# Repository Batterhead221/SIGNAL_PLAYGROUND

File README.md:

# signal_playground
(LIGHT_BOARD_TOY)
KIDS TOY BUILT FOR MY NIECE / ANALOG PROJECT

For Emerson - Electronics Learning Board
A small interactive PCB I designed as a hands-on electronics toy for my niece.
An educational analog hardware project.

•	Resistor = brightness control
•	Capacitor = smoothing
•	Inductor = energy storage

Press the switches and watch how each component changes the LED response in real time.

Key Features
•	Interactive LED response to different passive components
•	Dedicated channels for resistors, capacitors, and inductors
•	Through-hole component interfaces for easy experimentation
•	Custom silkscreen artwork and educational labeling
•	2-layer PCB with ground plane for noise reduction

Hardware Design
•	CAD: KiCad
•	Power: 2xAA battery holder (3V)
•	Grounding: Top & Bottom copper pour with stitched ground vias
•	Input Path: Noise-optimized routing with short trace to input capacitor

This was my first project, so it's not the prettiest and there are alot of things that I would have done different now.
Oh well, it worked, and my niece loved it.

DESIGNED & ENGINEERED BY BRANDON SHELLY

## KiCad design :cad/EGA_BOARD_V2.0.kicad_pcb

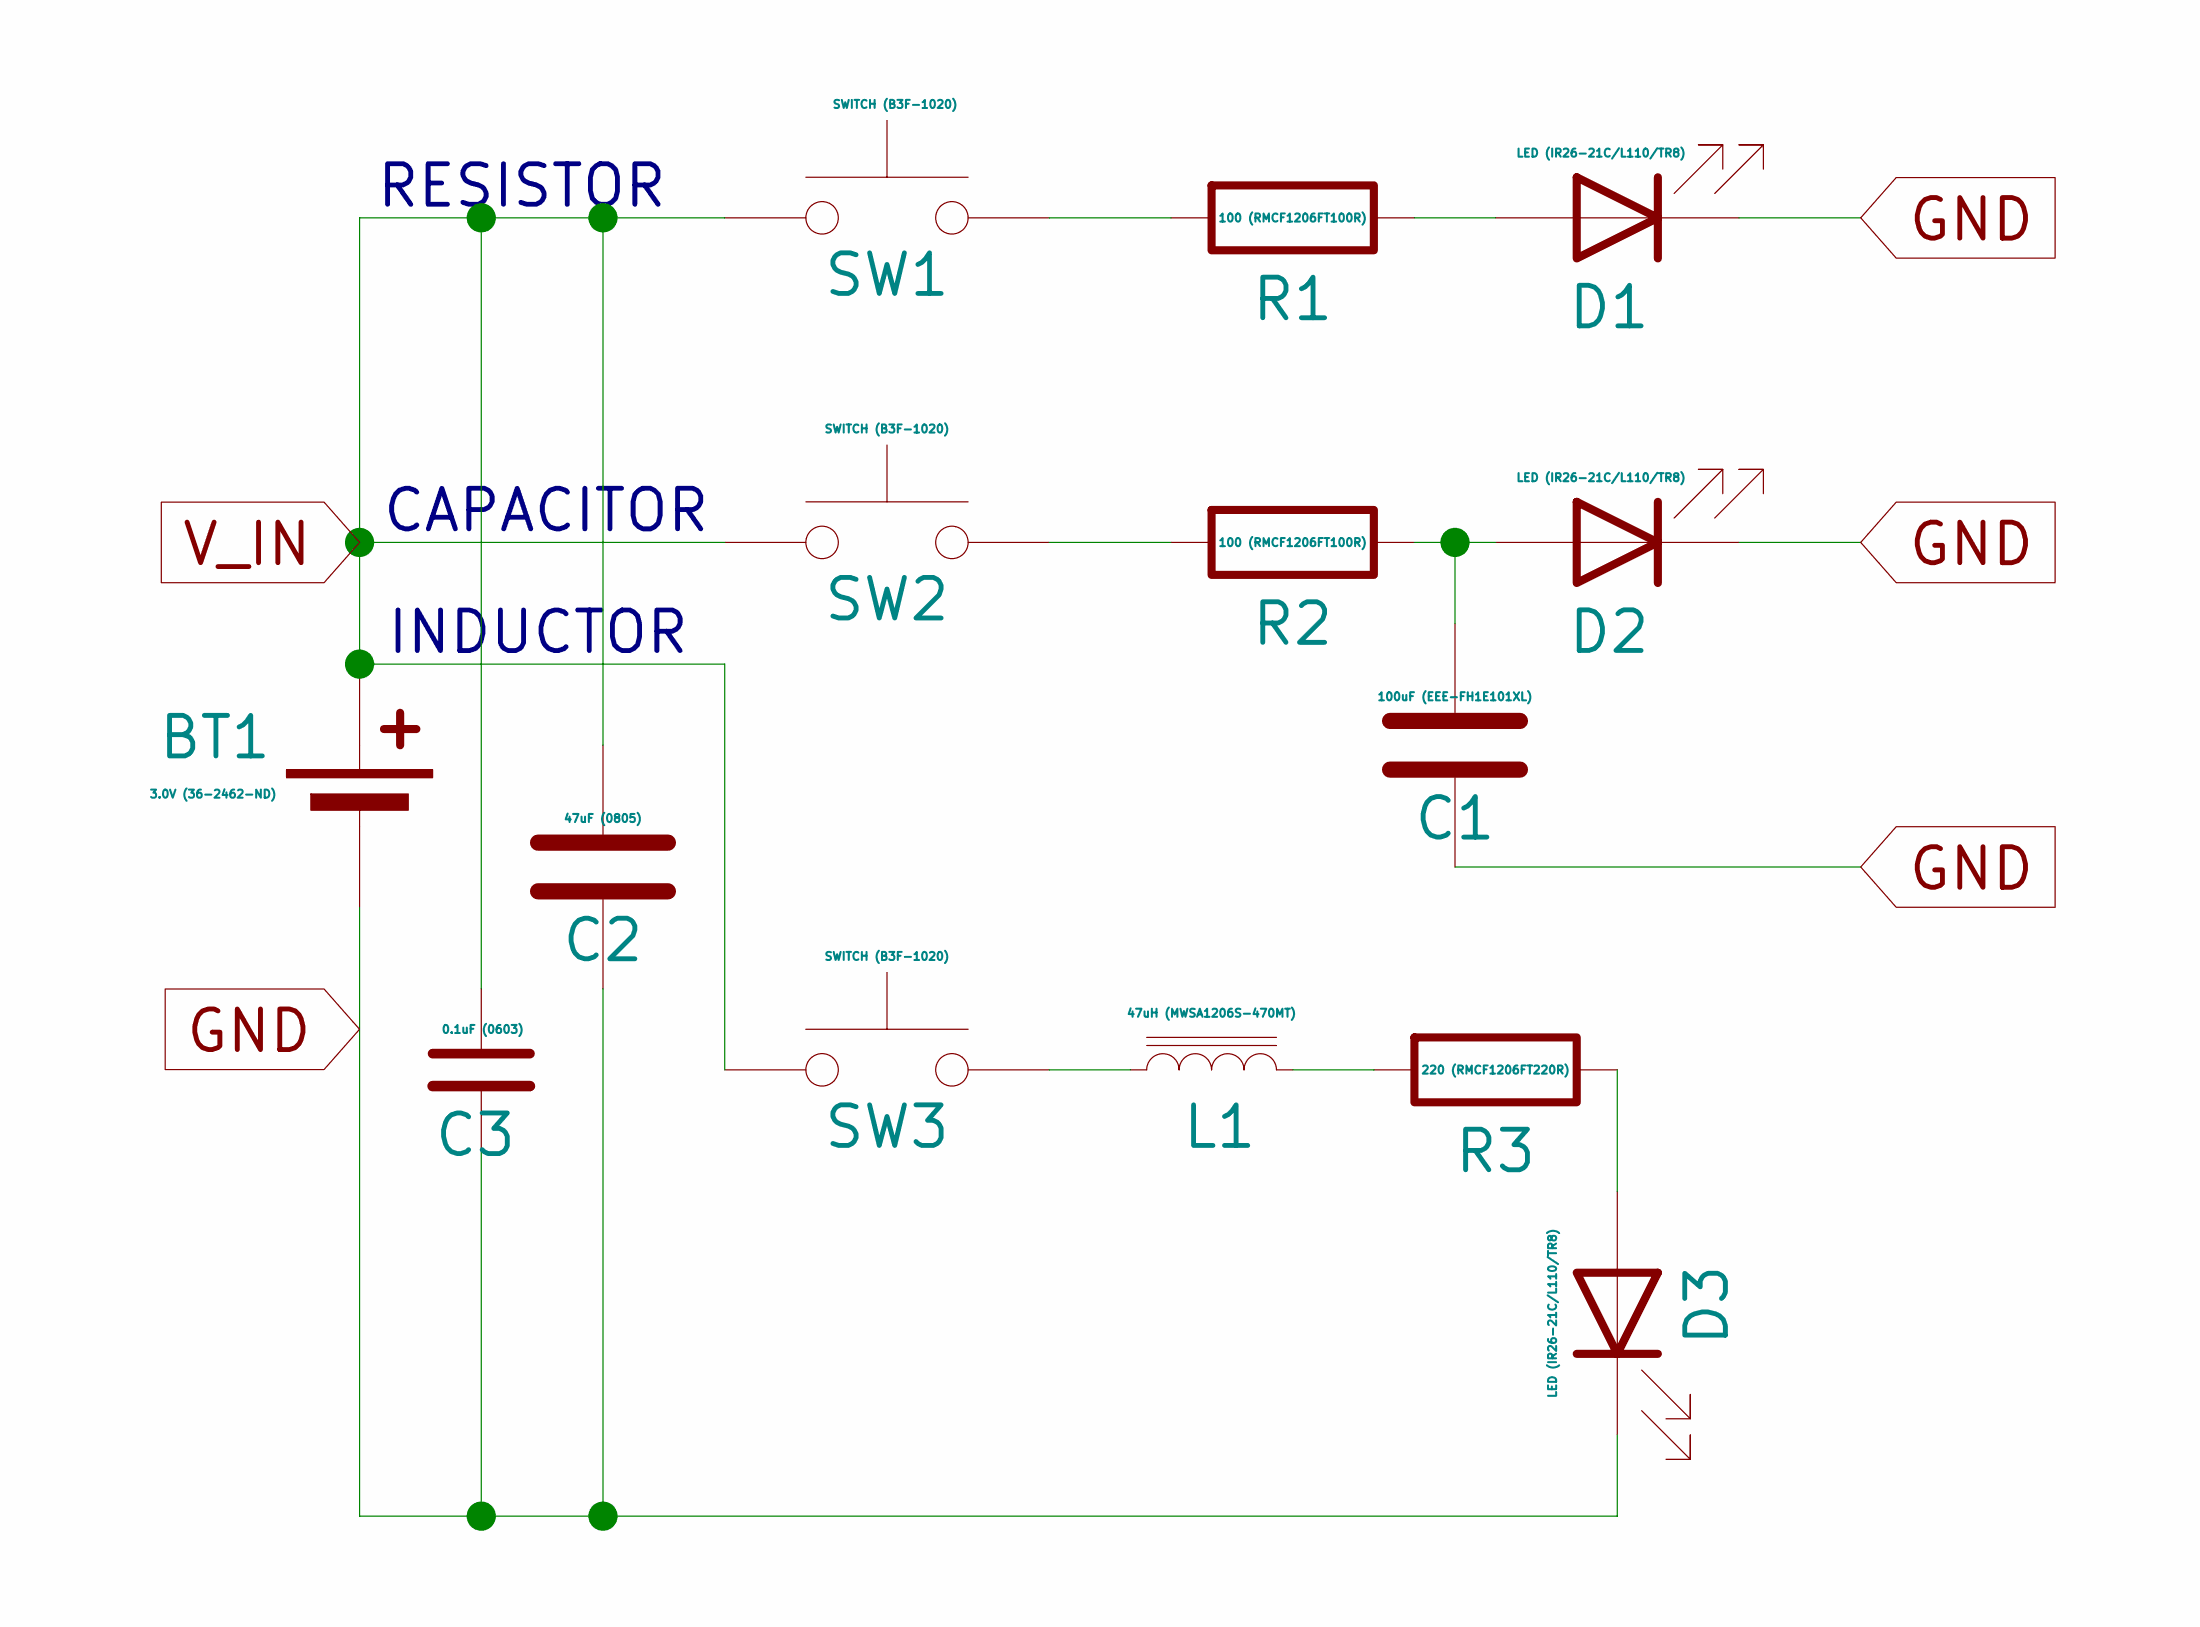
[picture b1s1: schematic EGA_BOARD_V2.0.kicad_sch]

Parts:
BT1: 3.0V (36-2462-ND); BatteryHolder_Keystone_2462_2xAA
C1: 100uF (EEE-FH1E101XL); C_Elec_5x5.8
C2: 47uF (0805); C_0805_2012Metric
C3: 0.1uF (0603); C_0603_1608Metric
D1, D2, D3: LED (IR26-21C/L110/TR8); LED_1206_3216Metric
L1: 47uH (MWSA1206S-470MT); L_Sunlord_MWSA1206S-3R3
R1, R2: 100 (RMCF1206FT100R); R_1206_3216Metric
R3: 220 (RMCF1206FT220R); R_1206_3216Metric
SW1, SW2, SW3: SWITCH (B3F-1020); SW_TH_Tactile_Omron_B3F-102x

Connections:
GND: BT1.2 (-), C1.2, C2.2, C3.2, D1.1 (K), D2.1 (K), D3.1 (K)
unnamed: D1.2 (A), R1.1
unnamed: C1.1, D2.2 (A), R2.1
unnamed: D3.2 (A), R3.1
unnamed: L1.1, SW3.2
unnamed: L1.2, R3.2
unnamed: R1.2, SW1.2
unnamed: R2.2, SW2.2
V_IN: BT1.1 (+), C2.1, C3.1, SW1.1, SW2.1, SW3.1

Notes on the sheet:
RESISTOR
INDUCTOR
CAPACITOR

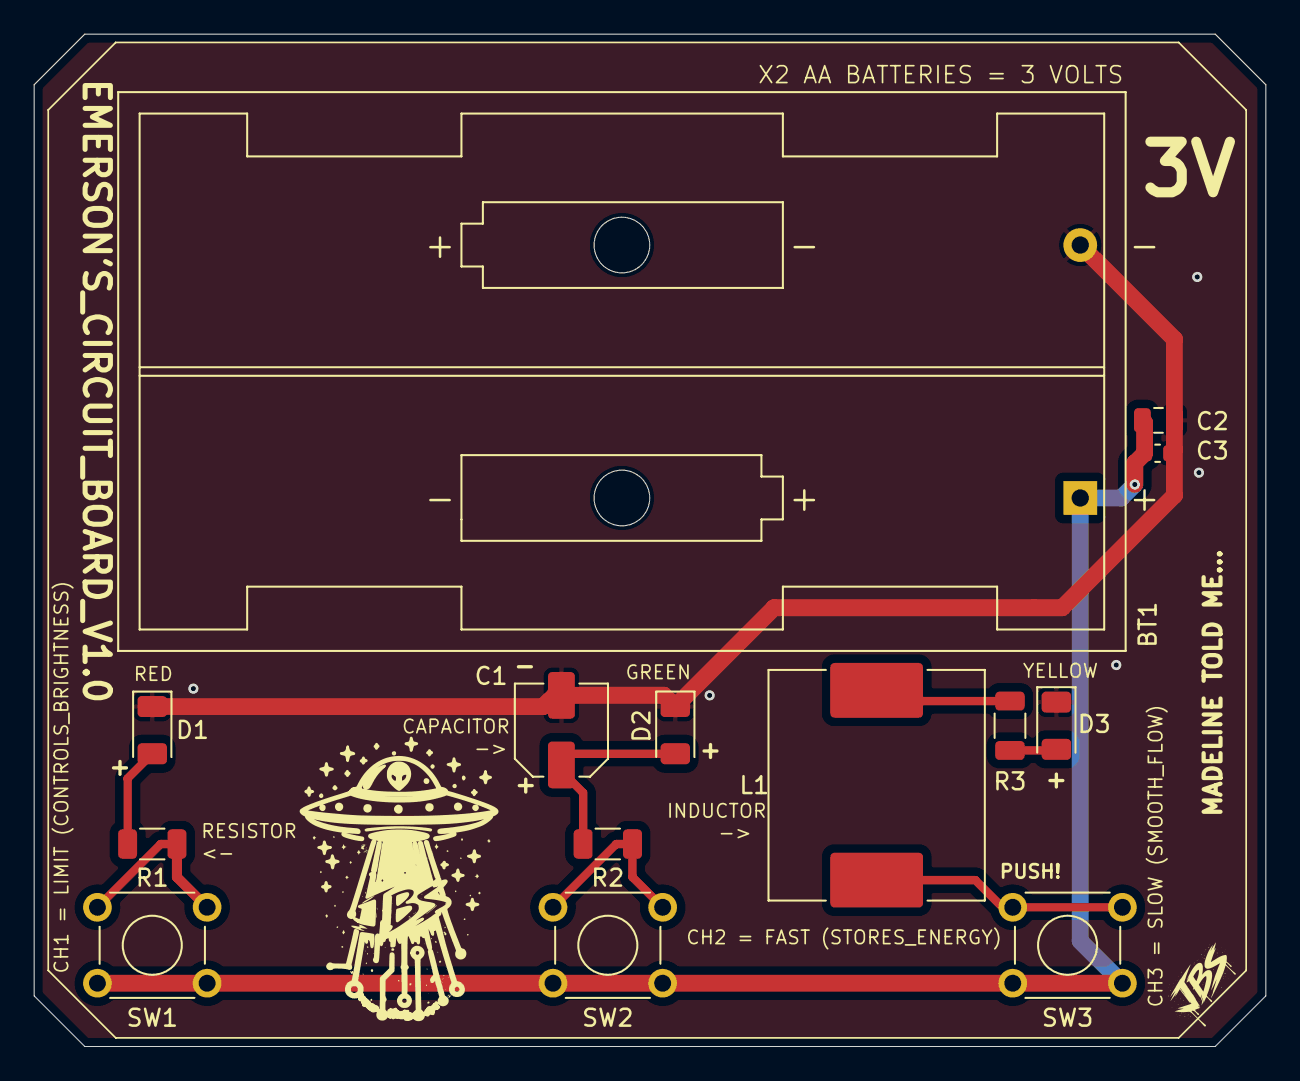
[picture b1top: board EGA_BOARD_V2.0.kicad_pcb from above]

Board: 2 copper layers, 73.0 x 60.0 mm, 14 parts (0 on the bottom side), 9 nets.

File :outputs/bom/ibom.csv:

Reference,Qty,Value,Footprint,Description
BT1,1,3.0V Battery Holder,BatteryHolder_Keystone_2462_2xAA,2xAA Battery Power Source
C1,1,100uF,C_Elec_5x5.8,Power Decoupling Capacitor
C2,1,47uF,C_0805_2012Metric,Signal Smoothing Capacitor
C3,1,0.1uF,C_0603_1608Metric,Op-Amp Bypass Capacitor
D1-D3,3,LED 1206,LED_1206_3216Metric,Visual Learning Indicators
L1,1,47uH Inductor,L_1206,Energy Storage Demonstration Component
R1-R?,Various 100Ω/220Ω,R_1206,Current Limiting & Feedback Network
SW1-SW3,3,Tactile Switch,B3F-1020,User Interaction / Component Selection
PCB,1,2-Layer FR4,Custom,Educational Component Learning Board

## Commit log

2026-02-13 4_EMERSON
    Educational PCB for my niece. Teaches how resistors, capacitors, and inductors affect LED behavior
2026-02-13 Renamed files + added POST_FAB .png
2026-02-15 UPDATE
    UPDATE
2026-03-20 REPO UPDATE
2026-04-18 file path restructure
2026-05-03 folder restructure
2026-05-07 EDITED BOARD
2026-05-13 Revised repo
